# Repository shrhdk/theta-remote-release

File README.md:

# THETA簡単リモコン

5秒でRICOH THETA Sと接続できる簡単リモコンの設計を公開しています。

## 機能

- THETA Sのシャッターを切る
- THETA Sの動画撮影開始/停止
- Webブラウザで接続するTHETA Sを設定
- Webブラウザでファームウェアをアップデート
- USB充電

詳細は[操作説明](doc/instruction-manual.md)を御覧ください。

## プロジェクト構成

```
theta-remote-release/
  |-- hardware/       回路図・基板図 (KiCad)
  |-- src/            ファームウェア (Arduino)
  |-- platformio.ini  PlatformIOのプロジェクトファイル
```

## ハードウェア

回路図、プリント基板は[KiCad](http://kicad.org/)で設計しました。

`hardware/theta-remote-release.pro`をKiCadで開いてください。

- [回路図](hardware/theta-remote-release.sch.svg)
- [部品リスト](hardware/parts.md)

## ファームウェア

このプロジェクトはArduino ([PlatformIO](http://platformio.org/))を利用しています。

次の手順でファームをビルドしてリモコンに書き込めます。

1. PCのシリアルポートとリモコンのDEBUGコネクタを接続
2. リモコンの電源ON
3. 次のコマンドを実行

```
# もしPlatformIOがなければインストールする (Pythonが必要です)
$ pip install -U pip setuptools     
$ pip install -U platformio

# このリポジトリをCloneする
$ git clone https://github.com/shrhdk/theta-remote-release.git

# ビルドしてリモコン(ESP8266)にアップロードする
$ cd theta-remote-release
$ pio run --target upload
```

## 組み立て例

- [基板表面](doc/front.jpg)
- [基板裏面](doc/back.jpg)

## License

- This project is released under the MIT license.

## 謝辞

このプロジェクトは以下のソフトウェア・資料を利用しています。

- [aJson](https://github.com/interactive-matter/aJson) Copyright (c) 2010, Interactive Matter, Marcus Nowotny
- [ここであえてのESP-WROOM-02用変換基板 - ゆるりとものづくり](http://monomake.hatenablog.com/entry/2015/08/12/esp-wroom-02/)

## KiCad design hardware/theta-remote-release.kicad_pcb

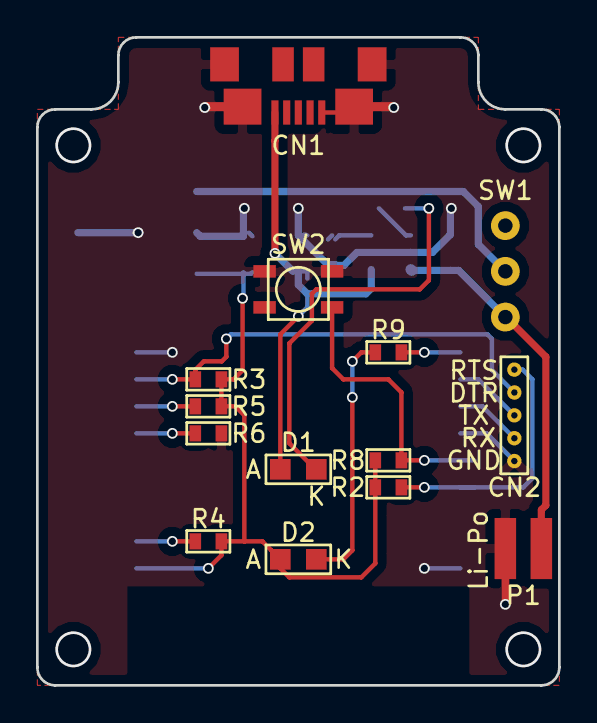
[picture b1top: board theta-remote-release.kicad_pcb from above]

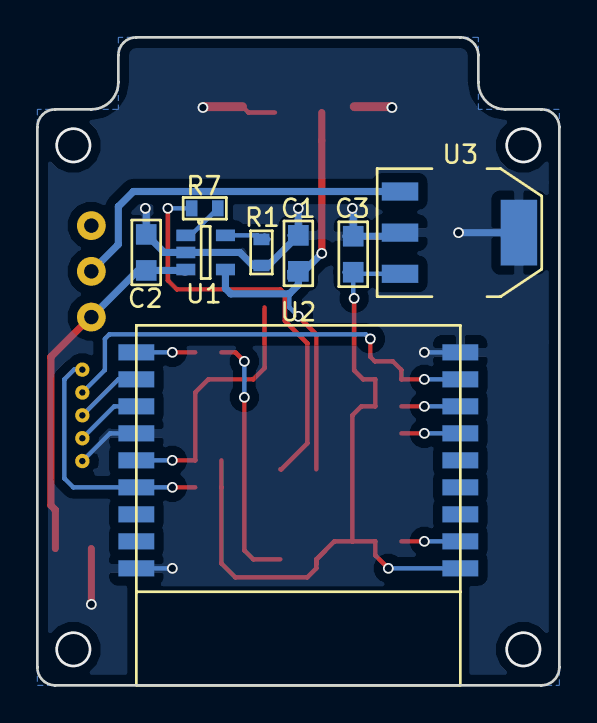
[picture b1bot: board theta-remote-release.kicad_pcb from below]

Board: 2 copper layers, 29.0 x 36.0 mm, 22 parts (8 on the bottom side), 18 nets.

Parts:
C1, C2, C3: 4.7uF; SMD2012
CN1: ZX62R-B-5P
CN2: DEBUG; Debug
D1: CHG; SMD2012_LED
D2: STAT; SMD2012_LED
P1: Li-Po 3.7V; Li-Po
R1, R2, R3, R4, R5, R6, R8: 10k; SMD1608
R7, R9: 100; SMD1608
SW1: POWER; ESP2020
SW2: SHUTTER; TVAF17-WEC-R
U1: MCP73831; SOT-23-5
U2: ESP-WROOM-02; esp-wroom-02
U3: MCP1825S-3002E/DB; SOT-223

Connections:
+3V: C3.1, D2.2, R2.1, R3.1, R4.1, R5.1, R8.1, U2.1, U3.3
+5V: C1.1, CN1.1, D1.2, U1.4
/CHG: R7.2, U1.1
/IO4: R9.2, U2.10
/IO5: R8.2, SW2.1, U2.14
GND: C1.2, C2.2, C3.2, CN1.5, CN1.6, CN2.5, P1.2, R1.1, R6.1, SW2.3, SW2.4, U1.2, U2.9, U2.13, U2.18, U3.2, U3.4
unnamed: C2.1, P1.1, SW1.3, U1.3
unnamed: CN2.1, R2.2, U2.15
unnamed: CN2.2, R3.2, U2.8
unnamed: CN2.3, U2.11
unnamed: CN2.4, U2.12
unnamed: D1.1, R7.1
unnamed: D2.1, R9.1
unnamed: R1.2, U1.5
unnamed: R4.2, U2.2
unnamed: R5.2, U2.7
unnamed: R6.2, U2.6
unnamed: SW1.2, U3.1

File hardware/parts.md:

# 部品リスト

| Ref. | Name            | Model/Value       | Package      | URL                                                                   |
|:----:|-----------------|-------------------|--------------|-----------------------------------------------------------------------|
| C1   | Capacitor       | 4.7uF             | 2012         | http://akizukidenshi.com/catalog/g/gP-07548/                          |
| C2   | Capacitor       | 4.7uF             | 2012         | http://akizukidenshi.com/catalog/g/gP-07548/                          |
| C3   | Capacitor       | 4.7uF             | 2012         | http://akizukidenshi.com/catalog/g/gP-07548/                          |
| CN1  | Micro USB Conn. | ZX62R-B-5P        |              | http://akizukidenshi.com/catalog/g/gC-05254/                          |
| CN2  | DEBUG           | Pin Socket        | 5pin, 1.27mm | http://akizukidenshi.com/catalog/g/gC-08695/                          |
| D1   | Orange LED      | OSO50805C1C       | 2012         | http://akizukidenshi.com/catalog/g/gI-06422/                          |
| D2   | Green LED       | OSG80805C1C       | 2012         | http://akizukidenshi.com/catalog/g/gI-06421/                          |
| R1   | Register        | 10k               | 1608         | http://akizukidenshi.com/catalog/g/gR-06103/                          |
| R2   | Register        | 10k               | 1608         | http://akizukidenshi.com/catalog/g/gR-06103/                          |
| R3   | Register        | 10k               | 1608         | http://akizukidenshi.com/catalog/g/gR-06103/                          |
| R4   | Register        | 10k               | 1608         | http://akizukidenshi.com/catalog/g/gR-06103/                          |
| R5   | Register        | 10k               | 1608         | http://akizukidenshi.com/catalog/g/gR-06103/                          |
| R6   | Register        | 10k               | 1608         | http://akizukidenshi.com/catalog/g/gR-06103/                          |
| R7   | Register        | 100               | 1608         | http://akizukidenshi.com/catalog/g/gR-06101/                          |
| R8   | Register        | 10k               | 1608         | http://akizukidenshi.com/catalog/g/gR-06103/                          |
| R9   | Register        | 100               | 1608         | http://akizukidenshi.com/catalog/g/gR-06101/                          |
| SW1  | Slide Switch    | ESP2020           | 3pin, 2.54mm | http://eleshop.jp/shop/g/gC5U122/                                     |
| SW2  | Push Switch     | TVAF17-WEC-R      |              | http://akizukidenshi.com/catalog/g/gP-08081/                          |
| U1   | Li-Po Charger   | MCP73831T-2ACI    | SOT-23-5     | http://www.aitendo.com/product/6258                                   |
| U2   | Processor       | ESP-WROOM-02      |              | http://akizukidenshi.com/catalog/g/gM-09607/                          |
| U3   | LDO Regulator   | MCP1825S-3002E/DB | SOT-223      | http://jp.rs-online.com/web/p/low-dropout-voltage-regulators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 |
| E1   | Li-Po Battery   | 110mAh            |              | https://www.switch-science.com/catalog/157/                           |

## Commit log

2015-12-16 Initial Commit
    Add hardware and code
2016-05-11 add reference
2016-05-11 add 1.0.0
2016-05-13 update readome
2016-05-24 add updateSession method
2016-05-24 use updateSession method instead of startSession
2016-05-24 move code about THETA to theta_s.cpp from main.ino
2016-05-24 remove gch files
2016-05-28 add ESP8266HTTPClient.cpp
2016-05-28 modify ESP8266HTTPClient.cpp
2016-05-28 use ESP8266HTTPClient
2016-05-28 support video mode and continuous shooting
2016-05-28 clear json buffer
2016-05-29 use ajson
2016-05-29 remove ArduinoJson
2016-05-29 update README.md about license.
2016-05-29 update copyright
2016-05-29 update README and DOCS
2016-06-04 remove redundant this->
2016-06-04 apply clang-format
2016-06-04 remove logger
2016-06-04 remove dead code
2016-06-23 mod README.md
2016-07-16 board = esp_wroom_02
2016-07-16 remove ESP8266HTTPClient.cpp. (https://github.com/esp8266/Arduino/pull/2060)
2016-07-16 remove redundant header including. (https://github.com/esp8266/Arduino/pull/2094)
2016-07-16 add change log
2016-12-30 update license
2017-12-29 fix URL for "ここであえてのESP-WROOM-02用変換基板"
2017-12-29 simplify gitignore
2017-12-29 add .piolibdeps/ to the gitignore
2021-11-10 Update README.md
    https://forum.kicad.info/t/warning-avoid-all-links-to-kicad-pcb-org-use-kicad-org/31521
